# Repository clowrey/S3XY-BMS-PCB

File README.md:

# isoSPI-M3Y-BMS-PCB

**Hardware Design for Tesla Model 3/Y Battery Management System**

This repository contains the **KiCad PCB design files** for a replacement Battery Management System (BMS) designed for Tesla Model 3 and Model Y battery packs. This hardware interfaces with high-voltage (400V) battery modules using the isoSPI protocol and provides comprehensive monitoring, control, and safety features.

🔗 **Companion Firmware Repository:** [isoSPI-M3Y-BMS](https://github.com/clowrey/isoSPI-M3Y-BMS)

---

## ⚡ Overview

This PCB design implements a complete BMS controller capable of:

- **Direct BMB Communication**: isoSPI master interface for Battery Management Boards
- **High Precision Monitoring**: Current, voltage, temperature, and power measurement
- **CAN Bus Integration**: 500kbps communication with vehicle systems and inverters
- **Contactor Control**: Safe sequenced activation of high-voltage contactors
- **Cell Balancing**: Individual cell balancing control through BMB modules
- **Safety Features**: Overcurrent, overvoltage, undervoltage, and thermal protection

### 🔋 Tesla Model 3/Y Battery Pack Architecture

Tesla Model 3 and Model Y battery packs utilize a modular architecture:

- **Cell Configuration:** 4416 cells (96s46p) in 4 modules
- **Module Configuration:** 24 cells in series per module (96 total series groups)
- **Nominal Voltage:** ~350V (fully charged: ~400V, discharged: ~280V)
- **Capacity:** Varies by pack (50-82 kWh depending on model/year)
- **Battery Management Boards (BMBs):** Each module contains BMBs that monitor cell groups
- **Communication:** Original packs use proprietary Tesla BMS; this project replaces it

**Why Replace the BMS?**
- Reuse Tesla packs in DIY electric vehicle conversions
- Second-life energy storage systems
- Research and educational purposes
- Open-source alternative to proprietary systems

### 🔌 Key Hardware Features

| Feature | Implementation |
|---------|----------------|
| **Microcontroller** | Raspberry Pi RP2354B (dual Cortex-M33, 150MHz) |
| **Current Sensing** | Texas Instruments INA228 (20-bit ADC) |
| **Pack Voltage** | 4-channel ADC with precision voltage dividers |
| **CAN Interface** | Hardware CAN transceiver (500kbps) |
| **isoSPI** | Differential Manchester encoding, galvanic isolation |
| **Contactor Drivers** | 4-channel PWM with inrush control |
| **Operating Voltage** | 12V nominal input |
| **High Voltage Rating** | Up to 400V DC battery pack |

---

## 📁 Repository Structure

```
isoSPI-M3Y-BMS-PCB/
├── isoSPI-M3Y-BMS-PCB.kicad_pro    # KiCad project file
├── isoSPI-M3Y-BMS-PCB.kicad_sch    # Main schematic design
├── isoSPI-M3Y-BMS-PCB.kicad_pcb    # PCB layout
├── BMS_Library/                     # Custom component library
│   ├── BMS_Library.kicad_sym        # Symbol library
│   └── BMS_Library.pretty/          # Footprint library
├── RP2350_KiCad/                    # RP2350 MCU resources
│   ├── RP2350A_QFN-60*.kicad_mod    # Footprints
│   ├── RP2350A-QFN60.step           # 3D model
│   └── rp2350a-qfn60.kicad_sym      # Symbol
├── bms.3dshapes/                    # 3D models for connectors
├── reassociate_components.py        # Component re-linking utility
├── apply_mapping.py                 # Reference mapping tool
└── fabrication-toolkit-options.json # Manufacturing outputs config
```

---

## 🚀 Getting Started

### Prerequisites

- **KiCad 8.0+** - [Download here](https://www.kicad.org/download/)
- **Python 3.7+** (for utility scripts)
- Basic understanding of PCB design and high-voltage safety

### Opening the Project

1. **Clone the repository:**
   ```bash
   git clone https://github.com/clowrey/isoSPI-M3Y-BMS-PCB.git
   cd isoSPI-M3Y-BMS-PCB
   ```

2. **Open in KiCad:**
   - Launch KiCad
   - Open `isoSPI-M3Y-BMS-PCB.kicad_pro`

3. **Library Configuration:**
   - Libraries are configured in local `sym-lib-table` and `fp-lib-table`
   - Project-specific libraries (`BMS_Library`, `RP2350_KiCad`) should load automatically
   - If missing components appear, verify library paths in KiCad preferences

### Viewing the Design

- **Schematic:** Open `isoSPI-M3Y-BMS-PCB.kicad_sch` to view circuit design
- **PCB Layout:** Open `isoSPI-M3Y-BMS-PCB.kicad_pcb` to view board layout
- **3D View:** Press `Alt+3` in PCB editor to visualize the assembled board

---

## 🛠️ Design Sections

### Power Supply
- 12V input with protection and filtering
- 3.3V LDO for MCU and logic
- Isolated power for isoSPI interface

### Microcontroller (RP2354B)
- QFN-60 package with thermal pad
- Crystal oscillator for precision timing
- JTAG/SWD debug interface
- Boot mode selection

### Current Sensing (INA228)
- Shunt resistor-based measurement
- 20-bit delta-sigma ADC
- Bidirectional current monitoring
- I2C interface to MCU

### Voltage Monitoring
- 4-channel pack voltage measurement
- Precision resistor dividers (high voltage to ADC range)
- Individual cell voltages via isoSPI
- 12-bit internal ADC

### isoSPI Interface
- Differential transformer coupling
- Manchester encoding via PIO
- Galvanic isolation from high voltage
- Master and snooper mode support

### CAN Bus
- Hardware CAN transceiver
- 120Ω termination (configurable)
- PIO-based CAN 2.0B implementation
- 500kbps operation

### Contactor Control
- 4 independent high-current outputs
- PWM inrush current limiting
- Sequenced activation logic
- Flyback protection diodes

### Connectors
- High-voltage battery pack connector
- 12V power input
- CAN bus connector
- USB programming interface
- Debug headers

---

## 🔧 Utility Scripts

### `reassociate_components.py`

Re-links PCB footprints to schematic symbols after copying design sections. This is essential when:
- Copying and pasting PCB sections (breaks UUID links)
- Duplicating circuits for multi-channel designs
- Recovering from schematic/PCB desynchronization

**Usage:**
```bash
python reassociate_components.py
```

The script:
1. Parses both `.kicad_sch` and `.kicad_pcb` files
2. Matches components by reference designator and type
3. Updates PCB footprints with correct schematic UUIDs
4. Creates backup before modification

### `apply_mapping.py`

Applies specific component reference remapping (e.g., when renaming U11→U27). Updates both reference designators and UUID linkages.

**Usage:**
```bash
python apply_mapping.py
```

---

## 📦 Manufacturing

### Generating Production Files

The project includes `fabrication-toolkit-options.json` for automated manufacturing output generation.

**Recommended manufacturers:**
- JLCPCB
- PCBWay
- OSH Park
- Any PCB fab supporting 4+ layer boards

### PCB Specifications

| Parameter | Value |
|-----------|-------|
| **Layers** | 4 (or as designed) |
| **PCB Thickness** | 1.6mm standard |
| **Copper Weight** | 2oz for power traces |
| **Min Trace/Space** | 6/6 mil (typical) |
| **Solder Mask** | Green (or preference) |
| **Silkscreen** | White |
| **Surface Finish** | ENIG or HASL |

### High-Voltage Considerations

⚠️ **CRITICAL SAFETY REQUIREMENTS:**

- **Clearances:** Maintain minimum 4mm creepage distance for 400V
- **Isolation:** isoSPI and current sensing must maintain galvanic isolation
- **Testing:** All HV sections require hi-pot testing before energization
- **Conformal Coating:** Recommended for high-voltage traces
- **Certifications:** May require UL/CE certification for commercial use

---

## 🔌 Assembly Notes

### Component Sourcing

- Most components available from Digi-Key, Mouser, or LCSC
- RP2354B: Available from Raspberry Pi approved distributors
- INA228: Texas Instruments or authorized distributors
- Connectors: Match to Tesla pack interface specifications

### Assembly Sequence

1. **SMD Components:** Reflow solder all surface mount parts
2. **Through-hole:** Hand solder connectors and large components
3. **Inspection:** Verify all solder joints and orientation
4. **Testing:** Low-voltage functional testing before HV connection
5. **Programming:** Flash firmware via USB or SWD
6. **Calibration:** ADC and current sensing calibration routines

---

## 🔗 Firmware Integration

This PCB is designed to work with the companion firmware:

📦 **[isoSPI-M3Y-BMS Firmware](https://github.com/clowrey/isoSPI-M3Y-BMS)**

### ✅ Implemented Features (v2.0.0)

**Hardware Drivers:**
- RP2354B microcontroller with dual Cortex-M33 cores
- INA228 current/voltage/power sensor driver
- Internal ADC for pack voltage monitoring (4 channels)
- Contactor control (4 channels, sequenced activation)
- Serial command processing (30+ commands)
- CAN bus interface (can2040, 500kbps broadcast)
- isoSPI PIO master implementation
- isoSPI passive bus snooper
- Unified BMB test interface
- Runtime interface switching (Batman/isoSPI)

**System Features:**
- Parameter system with 108+ BMS parameters
- Coulomb counting for SOC tracking
- Automatic 10Hz pack status CAN broadcasting
- Statistics tracking for TX/RX/errors
- Configurable message IDs and data formatting

### 🚧 In Progress (Phase 3)

- BATMan/isoSPI interface switching
- Runtime interface control (automatic disable/enable)
- Full BMS state machine
- Cell voltage reading via isoSPI
- Cell balancing control
- Temperature monitoring

### 📋 Pending (Phases 4-6)

- Hardware testing and validation
- Calibration routines for ADC
- Flash storage for calibration data
- Error handling and recovery
- Extended testing (24+ hours)
- Performance optimization
- Documentation completion

### Getting Started with Firmware

1. Clone the firmware repository
2. Install Pico SDK and build tools (CMake-based)
3. Build the project:
   ```bash
   cd isoSPI-M3Y-BMS
   mkdir build && cd build
   cmake ..
   make
   ```
4. Flash to RP2354B via USB or SWD
5. Connect via serial interface (115200 baud)
6. Configure using serial commands
7. Optional: Integrate with ESPHome for monitoring and display

### Optional: ESPHome Display Integration

The firmware supports integration with ESPHome for advanced monitoring via touchscreen displays:

**ESPHome Features:**
- **Three-Page Display Interface:**
  - Main overview with key parameters
  - Detailed battery information
  - Cell voltage graph (all 108 cells visualized)
- **Real-time Monitoring:** Live parameter updates every 5-10 seconds
- **Touch Controls:** Balance on/off, page navigation
- **Home Assistant Integration:** All BMS parameters as HA entities
- **Professional UI:** LVGL-based interface optimized for 480x320 displays

**Supported Hardware:**
- JC4832W535 480x320 QSPI touchscreen
- ESP32-S3 based display modules
- WiFi connectivity for OTA updates

See the [ESPHome interface documentation](https://github.com/clowrey/isoSPI-M3Y-BMS/tree/main/esphome-interface) in the firmware repository for setup instructions.

---

## ⚠️ Hardware Safety

### ⚡ HIGH VOLTAGE WARNING ⚡

**This system interfaces with 400V battery packs that can deliver LETHAL current.**

- **Only qualified personnel should work on high-voltage systems**
- **Proper isolation and safety measures required**
- **Use appropriate personal protection equipment (PPE)**
- **Follow all electrical safety protocols**
- **Discharge pack completely before service**
- **EV battery systems can deliver lethal current**
- **Follow all lockout/tagout procedures**

### ⚠️ DEVELOPMENT STATUS

- **This is a development version (v2.0.0)**
- **isoSPI implementation is experimental**
- **BATMan protocol partially implemented**
- **Extensive testing required before production use**
- **USE AT YOUR OWN RISK**
- No warranty expressed or implied
- Not certified for commercial EV use
- User assumes all responsibility for safety

### Recommended Safety Equipment

- Insulated high-voltage gloves (Class 00 minimum)
- Safety glasses with side shields
- Insulated tools rated for 1000V
- Multimeter rated for CAT III 600V or higher
- Isolation transformer for bench testing
- Emergency shutdown procedures
- First aid and emergency response plan

---

## 📚 Documentation

### Related Resources

- **Firmware Repository:** [isoSPI-M3Y-BMS](https://github.com/clowrey/isoSPI-M3Y-BMS)
- **RP2354B Datasheet:** [Raspberry Pi Documentation](https://datasheets.raspberrypi.com/rp2350/rp2350-datasheet.pdf)
- **INA228 Datasheet:** [Texas Instruments](https://www.ti.com/product/INA228)
- **Pico SDK:** [Raspberry Pi Pico SDK](https://github.com/raspberrypi/pico-sdk)
- **can2040 Library:** [Kevin O'Connor's can2040](https://github.com/KevinOConnor/can2040)
- **Original BATMan BMS:** Damien Maguire & Tom de Bree

### Additional Documentation

- Schematic PDF exports (generate from KiCad)
- Bill of Materials (generate from KiCad BOM tool)
- Assembly drawings (generate from KiCad fabrication outputs)
- Test procedures (in firmware repository)
- CAN message format documentation (in firmware repo)
- Calibration procedures (in firmware repo)

---

## 🤝 Contributing

Contributions are welcome! Please:

1. Fork the repository
2. Create a feature branch (`git checkout -b feature/improvement`)
3. Make your changes with clear commit messages
4. Test thoroughly (especially high-voltage sections)
5. Submit a pull request with detailed description

**Areas for contribution:**
- Schematic improvements
- PCB layout optimization
- Additional protection circuits
- Manufacturing DFM improvements
- Documentation enhancements
- Test jig designs

---

## 📝 License

This project is licensed under the **GNU General Public License v3.0** - see the [LICENSE](LICENSE) file for details.

This program is free software: you can redistribute it and/or modify it under the terms of the GNU General Public License as published by the Free Software Foundation, either version 3 of the License, or (at your option) any later version.

This program is distributed in the hope that it will be useful, but WITHOUT ANY WARRANTY; without even the implied warranty of MERCHANTABILITY or FITNESS FOR A PARTICULAR PURPOSE. See the GNU General Public License for more details.

**In summary:**
- ✅ Free to use, modify, and distribute
- ✅ Must disclose source code
- ✅ Must use same GPL-3.0 license
- ✅ State changes made to original
- ❌ No warranty provided

---

## 🙏 Acknowledgments

- **Damien Maguire & Tom de Bree** - Original BATMan BMS software
- **ESPHome Community** - Framework and component support
- **Kevin O'Connor** - can2040 library for RP2040/RP2350
- **Raspberry Pi Foundation** - Pico SDK and excellent documentation
- **Texas Instruments** - INA228 current sensing IC
- **KiCad Community** - Excellent open-source EDA tools
- **Analog Devices** - isoSPI protocol and reference designs
- **Tesla Motors** - Battery module architecture reference

---

## 📧 Support & Contact

- **Issues:** Use GitHub Issues for bug reports and feature requests
- **Discussions:** GitHub Discussions for general questions
- **Pull Requests:** Contributions welcome via GitHub PR

---

## 📋 Changelog

### Hardware Version 2.0 (December 2025) - RP2354B Platform

**Complete platform migration supporting firmware v2.0.0:**

#### **Major Hardware Changes**

* **Microcontroller:** Migrated from ESP32 to Raspberry Pi RP2354B
  - Dual Cortex-M33 cores @ 150MHz
  - QFN-60 package with thermal management
  - Native USB support for programming and debugging
  - Hardware SWD debug interface

* **Current Sensing:** Replaced AS8510 with Texas Instruments INA228
  - 20-bit delta-sigma ADC
  - High-side and low-side sensing capability
  - I2C interface with configurable address
  - Integrated power calculation

* **Pack Voltage Monitoring:** Added 4-channel internal ADC monitoring
  - Precision voltage dividers for 400V → 3.3V range
  - 12-bit resolution
  - Individual channel filtering

* **CAN Bus:** Integrated hardware CAN transceiver
  - Native CAN 2.0B support via PIO
  - 500kbps operation
  - Configurable termination (120Ω)

#### **New Features**

* **isoSPI Implementation:**
  - Differential transformer coupling with galvanic isolation
  - PIO-based Manchester encoding/decoding
  - Master mode for direct BMB communication
  - Passive snooper mode for bus monitoring
  - Runtime switching between BATMan SPI and isoSPI

* **Enhanced Contactor Control:**
  - 4-channel PWM drivers with inrush limiting
  - Sequenced activation logic in hardware
  - Flyback protection for inductive loads

* **Unified Testing Interface:**
  - Single test connector for both BATMan and isoSPI modes
  - Automatic interface detection

#### **Firmware Compatibility**

This hardware revision requires **firmware v2.0.0 or later** from the companion repository:
- [isoSPI-M3Y-BMS v2.0.0 Changelog](https://github.com/clowrey/isoSPI-M3Y-BMS#changelog)

### Hardware Version 1.x (2024-2025) - ESP32 Platform

**Original ESP32-based design:**
- ESP32-WROOM-32 microcontroller
- AS8510 current sensor
- Arduino framework
- BATMan SPI communication only
- ESPHome integration support

---

## ⚙️ Project Status

**Current Hardware Version:** v2.0 (RP2354B-based design)

**PCB Development Status:**
- ✅ Schematic design complete
- ✅ Component selection finalized
- 🔄 PCB layout in progress
- ⏳ Design rule check (DRC) pending
- ⏳ Prototype fabrication pending
- ⏳ Hardware validation pending
- ⏳ Production testing pending

**Companion Firmware Status:** 
- **Version:** v2.0.0 (November 2025)
- **Status:** Active development
- **Phase:** isoSPI implementation in progress (Phase 3)
- **See:** [Firmware Repository](https://github.com/clowrey/isoSPI-M3Y-BMS) for detailed status

---

## 🔮 Future Enhancements

- [ ] Enhanced thermal management
- [ ] Additional redundant safety circuits
- [ ] Wireless monitoring interface
- [ ] Integrated display option
- [ ] Automotive-grade component variants
- [ ] Extended temperature range support
- [ ] Multi-pack support with CAN bridging
- [ ] Production test fixture design

---

**⚡ Building the future of open-source battery management systems ⚡**

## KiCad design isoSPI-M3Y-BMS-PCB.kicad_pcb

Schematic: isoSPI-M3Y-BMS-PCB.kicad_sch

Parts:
BT1, BT3, BT4, BT5, BT6, BT7, BT8, BT9: ~100V Brick
C1, C2, C55, C57: 10uF; C_0805_2012Metric; Voltage 50V; JLCPCB Part # C440198
C3, C4: 4.7uF 50V; C_1206_3216Metric; JLCPCB Part # C29823
C5, C94: 100nf; C_0603_1608Metric_Pad1.08x0.95mm_HandSolder; JLCPCB Part # C14663
C6, C24, C29: 10uF; C_0805_2012Metric; Voltage 50V X5R; JLCPCB Part # C440198
C7, C9, C49, C50, C51, C52, C62, C95, C132: 22uF; C_0805_2012Metric; Voltage 25V X5R; JLCPCB Part # C45783
C8: 10uF; C_0805_2012Metric_Pad1.18x1.45mm_HandSolder; Voltage 50V; JLCPCB Part # C440198
C10, C41, C42, C43: 100nf; C_0603_1608Metric; JLCPCB Part # C14663
C11, C38: 22uF; C_0805_2012Metric_Pad1.18x1.45mm_HandSolder; Voltage 25V; JLCPCB Part # C45783
C12, C13, C14, C15, C16, C21, C22, C23, C25, C28, C33, C44, C45, C54, C79, C80, C81, C82, C85: 100nF; C_0603_1608Metric; JLCPCB Part # C14663
C17, C19, C20, C86: 1uF; C_0603_1608Metric; JLCPCB Part # v
C18: 1uF; C_0603_1608Metric; JLCPCB Part # C15849
C26, C40: 1uF; C_0603_1608Metric_Pad1.08x0.95mm_HandSolder; JLCPCB Part # C15849
C27, C32, C47, C61, C69, C72: 4.7u; C_0402_1005Metric; JLCPCB Part # C23733
C30, C31, C68: 100pF; C_0603_1608Metric; JLCPCB Part # C14858
C34, C112: 680uF; CP_Radial_D10.0mm_P5.00mm; Voltage 35V Polymer
C35, C36, C117, C118: 15pF; C_0402_1005Metric; JLCPCB Part # C1548
C37, C48, C87, C89: 4.7u; C_0402_1005Metric_small_pads; JLCPCB Part # C23733
C39, C56: 100nF; C_0603_1608Metric_Pad1.08x0.95mm_HandSolder; JLCPCB Part # C14663
C46, C58, C59, C60, C63, C64, C65, C66, C67, C70, C71, C73, C74, C75, C78, C120, C123, C124, C126, C127, C128, C129, C130, C131: 100n; C_0402_1005Metric; JLCPCB Part # C1525
C53: 4.7uF; C_0603_1608Metric; JLCPCB Part # C19666
D1, D7, D10, D25: SM15T36CA; D_SMC; JLCPCB Part # C1976312
D2, D3, D4, D8, D19, D38: Green; LED_0805_2012Metric; JLCPCB Part # C2297
D5, D23, D26, D29, D31, D32, D40: White; LED_0805_2012Metric; JLCPCB Part # C34499
D6, D9, D11, D14, D15, D21, D24, D30, D36, D39, D53: SS54; D_SMA; JLCPCB Part # C22452
D12, D13, D16, D17, D18, D20, D22, D27, D41, D42, D49, D50, D51: SMB6.8CA; D_SMB; JLCPCB Part # C78395
D28, D33, D34, D37: Red; LED_0805_2012Metric; JLCPCB Part # C84256
F1, F8: Pyro Fuse
F9, F11: 63A HV DC
FB1, FB7: 120Ω@100MHz; C_0603_1608Metric; JLCPCB Part # C14709
FB5: 600R@100MHz; L_0603_1608Metric_Pad1.05x0.95mm_HandSolder; JLCPCB Part # C1002
FL3: SDCW3225S-2-102TF; FILTER-SMD_4P-L3.2-W2.5-BL; JLCPCB Part # C192586
H1, H2, H3, H4, H5, H7, H12, H13: MountingHole_Pad; MountingHole_6.5mm
J1, J10: Screw_Terminal_01x04; PhoenixContact_MC_1,5_4-G-3.81_1x04_P3.81mm_Horizontal
J2, J13: Conn_02x10_Odd_Even; PinHeader_2x10_P2.54mm_Vertical
J3: 8P8C_LED_Shielded_x2; RJ45_Amphenol_RJHSE538X-02; JLCPCB Part # C3010546
J5: OEM Shunt Connector; CONN_ZE05H-8DP-2H_HIR
J6: 349128020; CONN_SD-34912-001_02_MOL; JLCPCB Part # C587318
J7: OEM HV Sense Connector; CONN_173864-1_TYC
J8: OEM Connector; S44BRAD1AK
J9, J16: Conn_01x03; PinHeader_1x03_P2.54mm_Vertical
J11: Screw_Terminal_01x03; PhoenixContact_MC_1,5_2-G-3.81_1x02_P3.81mm_Horizontal
J12: Screw_Terminal_01x08; PhoenixContact_MC_1,5_8-G-3.81_1x08_P3.81mm_Horizontal
J14: Screw_Terminal_01x04; PhoenixContact_GMSTBA_2,5_4-G-7,62_1x04_P7.62mm_Horizontal
J15, J17, J18: USB_C_Receptacle_USB2.0_16P; USB_C_Receptacle_HRO_TYPE-C-31-M-12
JP1, JP2, JP7, JP8, JP9: SolderJumper_3_Bridged12; SolderJumper-3_P1.3mm_Bridged12_RoundedPad1.0x1.5mm_NumberL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
JP3, JP4, JP5, JP6, JP13, JP14: SolderJumper_3_Open; SolderJumper-3_P1.3mm_Open_RoundedPad1.0x1.5mm_NumberLabels
JP10, JP11, JP12: Jumper_2_Open; SolderJumper-2_P1.3mm_Open_RoundedPad1.0x1.5mm
K9, K14: Link Positive
K10, K16: FC Positive
K11, K17: FC Negative
K12, K15: Link Negative
K13, K18: Inverter
L1, L2, L4, L5: 6.8uh; L_Changjiang_FXL0630; JLCPCB Part # C167221
L3, L8: 22uh 5.5A; L_Changjiang_FXL1040; JLCPCB Part # C475917
L6, L7: 3.3u; L_pol_2016
Q1, Q2, Q3, Q5: CRSM034N06L2; AO_DFN-8-1EP_5.55x5.2mm_P1.27mm_EP4.12x4.6mm; JLCPCB Part # C467174
R1, R10: 150r; R_0603_1608Metric; JLCPCB Part # C22808
R2, R8: 2.2k; R_0603_1608Metric; JLCPCB Part # C4190
R3, R11, R27, R40, R41, R45, R47, R70, R74, R146: 24k; R_0603_1608Metric; JLCPCB Part # C23352
R4, R17, R25, R28, R62, R150: 100k; R_0603_1608Metric; JLCPCB Part # C25803
R5, R6, R26, R69, R90: 100R; R_0603_1608Metric; JLCPCB Part # C22775
R7, R9, R111, R112, R141: 510r; R_0603_1608Metric; JLCPCB Part # C23193
R12, R13, R14, R15, R20, R44, R53, R55, R82, R85, R174, R175: 5.1k; R_0603_1608Metric; JLCPCB Part # C23186
R16, R29, R48, R54, R56, R60, R66, R67, R68, R75, R77, R79, R83, R84, R140, R142, R143, R144, R148, R190: 10k; R_0603_1608Metric; JLCPCB Part # C25804
R18: 120r; R_1206_3216Metric; JLCPCB Part # C17909
R19, R33, R50, R58, R80, R171: 33r; R_0402_1005Metric; JLCPCB Part # C25105
R21, R24, R51, R52: 22R; R_0402_1005Metric; JLCPCB Part # C25092
R22, R31, R81: 10k; R_0603_1608Metric_Pad0.98x0.95mm_HandSolder; JLCPCB Part # C25804
R23, R36, R37, R38, R39, R42: 1.8k; R_0603_1608Metric; JLCPCB Part # C4177
R30: 100r; R_0603_1608Metric; JLCPCB Part # C22775
R32, R178: 25296nΩ
R34, R35, R43, R46, R49, R57, R59, R63, R64, R167, R168, R170: 1k; R_0402_1005Metric; JLCPCB Part # C11702
R61: 3k; R_0603_1608Metric; JLCPCB Part # C4211
R65: 2.7k; R_0603_1608Metric; JLCPCB Part # C13167
R94, R97: 1k; R_0603_1608Metric; JLCPCB Part # C21190
R98, R99, R100, R101, R102, R103, R104, R105, R106, R107, R108, R109, R110, R114, R115, R116, R126, R127, R130, R131, R134, R135, R153, R155, R193, R194, R195, R196, R214, R215, R216, R217, R218, R219, R220, R221, R222, R223, R224, R225, R226, R227: 1M; R_1206_3216Metric; JLCPCB Part # C17927
R149, R228, R229: 220r; R_0603_1608Metric; JLCPCB Part # C22962
R176: 27R 50W
SW1, SW2, SW3, SW4: TS-1187A-B-A-B; SW_Push_1P1T_XKB_TS-1187A; JLCPCB Part # C318884
TH1, TH2, TH3, TH4, TH5, TH6: B59451C1130B070; RV_Disc_D15.5mm_W7.5mm_P5.0mm; JLCPCB Part # C2762811
TP1, TP2, TP3, TP4, TP5, TP6, TP7, TP8, TP9, TP15, TP17, TP18: TestPoint_2Pole; TestPoint_2Pads_Pitch2.54mm_Drill0.9mm
TP10, TP11, TP12, TP13, TP14: TP; TestPoint_THTPad_D1.5mm_Drill1.0mm
TR10: HM2113ZNLT; JLCPCB Part # C5730533
U1, U15, U23, U25, U26: SN74LV1T08DBVR; SOT-23-5; JLCPCB Part # C2682144
U2, U4, U30: ISO1540; SOIC-8_3.9x4.9mm_P1.27mm; JLCPCB Part # C179739
U3: INA228; VSSOP-10_3x3mm_P0.5mm; JLCPCB Part # C5214669
U6, U22, U24: F0505S-1WR3; Converter_DCDC_TRACO_TEA1-xxxxHI_THT; JLCPCB Part # C7465182
U8, U9, U10, U20: LTV-217-B-G; SSOP-4_4.4x2.6mm_P1.27mm; JLCPCB Part # C115450
U11, U27: RP2354B; RP2350-QFN-80-1EP_10x10_P0.4mm_EP3.4x3.4mm_ThermalVias; JLCPCB Part # C39843328
U12: ADS1115; TSSOP-10_3x3mm_P0.5mm; LCSC Part # C37593
U13: ISO1050DUB; SOP-8_6.62x9.15mm_P2.54mm; LCSC Part # C16428
U16: BatMan; LQFP-64_10x10mm_P0.5mm; JLCPCB Part # DNP
U17: TPS5430DDAR; TI_SO-PowerPAD-8_ThermalVias; LCSC Part C9864
U21: AMS1117-3.3; SOT-223-3_TabPin2; JLCPCB Part # C6186
U28: AM26LV32EIDR; SOIC-16_3.9x9.9mm_P1.27mm; JLCPCB Part # C527448
U29: B0505S-3WR2; Converter_DCDC_TRACO_TRA3-xxxx_THT; LCSC Part # C7500927
U32: SP3485EN-L/TR; SOIC-8_3.9x4.9mm_P1.27mm; JLCPCB Part # C8963
Y1, Y2: ABM8-272-T3; Crystal_SMD_3225-4Pin_3.2x2.5mm; JLCPCB Part # C20625731

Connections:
3.3V Sense: R66.2, R67.1, U27.49 (GPIO40_ADC0)
5V Sense: R140.1, R146.2, U27.52 (GPIO41_ADC1)
+1V1: C48.1, C71.1, C120.1, C123.1, L7.1, U27.10 (DVDD), U27.32 (DVDD), U27.51 (DVDD), U27.65 (VREG_FB)
+1V1_2: C46.1, C58.1, C70.1, C87.1, L6.1, U11.10 (DVDD), U11.32 (DVDD), U11.51 (DVDD), U11.65 (VREG_FB)
+3.3V: C13.1, C14.1, C37.1, C53.2, C59.1, C60.1, C63.1, C64.1, C65.1, C66.1, C67.1, C73.1, C74.1, C75.1, C78.1, C89.1, C124.1, C126.1, C127.1, C128.1, C129.1, C130.1, C131.1, J2.1, J2.3, J2.5, J2.7, J2.9, J13.1, J13.3, J13.5, J13.7, J13.9, R12.1, R13.1, R19.2, R33.2, R50.2, R58.2, R59.1, R65.2, R66.1, R75.1, R82.1, R85.1, R94.1, TP7.2, U2.1 (VCC1), U4.1 (VCC1), U8.4, U9.4, U11.5 (IOVDD), U11.15 (IOVDD), U11.24 (IOVDD), U11.29 (IOVDD), U11.41 (IOVDD), U11.50 (IOVDD), U11.60 (IOVDD), U11.64 (VREG_VIN), U11.68 (USB_OTP_VDD), U11.69 (QSPI_IOVDD), U11.76 (IOVDD), U13.1 (VCC1), U21.2 (VO), U27.5 (IOVDD), U27.15 (IOVDD), U27.24 (IOVDD), U27.29 (IOVDD), U27.41 (IOVDD), U27.50 (IOVDD), U27.60 (IOVDD), U27.64 (VREG_VIN), U27.68 (USB_OTP_VDD), U27.69 (QSPI_IOVDD), U27.76 (IOVDD), U30.1 (VCC1)
+3V3: C21.1, C22.2, C25.1, U1.5 (VCC), U28.4 (G), U28.16 (VDD), U32.8 (VCC)
+5V: C9.2, C11.2, C23.1, C49.2, C50.2, C52.2, C79.2, C80.2, C81.2, C82.2, C112.1, C132.2, FB1.2, FB7.2, L1.2, L2.2, L4.2, L5.2, L8.1, R60.1, R146.1, R190.1, TP8.2, U15.5 (VCC), U16.5 (5V), U16.41 (5V), U16.47 (5V), U21.3 (VI), U23.5 (VCC), U25.5 (VCC), U26.5 (VCC)
/CAN 5V: C6.2, C16.2, R23.2, R37.2, R77.1, R112.1, U13.8 (VCC2), U24.7 (+Vout)
/CAN H: C30.2, D16.2 (A2), FL3.2, JP1.3 (B), JP2.1 (A), JP3.3 (B), JP4.3 (B), JP5.3 (B), JP6.3 (B), JP13.3 (B), JP14.3 (B), R18.2, TP2.2
/CAN L: C31.1, D17.1 (A1), FL3.3, JP1.1 (A), JP2.3 (B), JP3.1 (A), JP4.1 (A), JP5.1 (A), JP6.1 (A), JP13.1 (A), JP14.1 (A), R18.1, TP2.1
/Contactor_Input: D15.2 (A), D20.2 (A2), D36.2 (A), J1.2
/FC Pos: K10.13, K16.13, K18.1, R176.2, TH1.2, TH2.2, TH3.2
/FC-Neg-Jumper: C44.2, D19.1 (K), D25.2 (A2), D39.2 (A), JP10.1 (A), JP11.1 (A), JP12.1 (A), Q3.5 (D)
/GPIO0: R57.2, U27.77 (GPIO0)
/GPIO1: R63.2, U27.78 (GPIO1)
/GPIO2: R64.2, U27.79 (GPIO2)
/GPIO3: U27.80 (GPIO3)
/GPIO4: J2.2, U27.1 (GPIO4)
/GPIO5: J2.4, U27.2 (GPIO5)
/GPIO6: J2.6, U27.3 (GPIO6)
/GPIO7: J2.8, U27.4 (GPIO7)
/GPIO8: J2.10, U27.6 (GPIO8)
/GPIO9: J2.12, U27.7 (GPIO9)
/GPIO10: J2.14, U27.8 (GPIO10)
/GPIO11: J2.16, U27.9 (GPIO11)
/GPIO12: J2.18, U27.11 (GPIO12)
/GPIO13: J2.20, U27.12 (GPIO13)
/GPIO14: U27.13 (GPIO14)
/GPIO15: U27.14 (GPIO15)
/GPIO16: U27.16 (GPIO16)
/GPIO17: U27.17 (GPIO17)
/GPIO18: U27.18 (GPIO18)
/GPIO19: U27.19 (GPIO19)
/GPIO20: U27.20 (GPIO20)
/GPIO21: U27.21 (GPIO21)
/GPIO22: U27.22 (GPIO22)
/GPIO23: U27.23 (GPIO23)
/GPIO24: U27.25 (GPIO24)
/GPIO25: R48.1, U27.26 (GPIO25)
/GPIO44_ADC4: U27.55 (GPIO44_ADC4)
/GPIO45_ADC5: U27.56 (GPIO45_ADC5)
/GPIO46_ADC6: U27.57 (GPIO46_ADC6)
/GPIO47_ADC7: U27.58 (GPIO47_ADC7)
/Grn: J3.6, JP14.2 (C)
/HV Sense 5V: C18.2, C39.2, C56.2, FB5.2, R20.1, R44.1, R54.1, R81.2, R228.1, U2.8 (VCC2), U12.8 (VDD)
/Logic_Input: D12.2 (A2), D14.2 (A), J1.4
/MCU2_GPIO0: R59.2, U11.77 (GPIO0)
/MCU2_GPIO3: U11.80 (GPIO3)
/MCU2_GPIO4: J13.2, U11.1 (GPIO4)
/MCU2_GPIO5: J13.4, U11.2 (GPIO5)
/MCU2_GPIO6: J13.6, U11.3 (GPIO6)
/MCU2_GPIO7: J13.8, U11.4 (GPIO7)
/MCU2_GPIO8: J13.10, U11.6 (GPIO8)
/MCU2_GPIO9: J13.12, U11.7 (GPIO9)
/MCU2_GPIO10: J13.14, U11.8 (GPIO10)
/MCU2_GPIO11: J13.16, U11.9 (GPIO11)
/MCU2_GPIO12: J13.18, U11.11 (GPIO12)
/MCU2_GPIO13: J13.20, U11.12 (GPIO13)
/MCU2_GPIO15: U11.14 (GPIO15)
/MCU2_GPIO16: U11.16 (GPIO16)
/MCU2_GPIO17: U11.17 (GPIO17)
/MCU2_GPIO18: U11.18 (GPIO18)
/MCU2_GPIO19: U11.19 (GPIO19)
/MCU2_GPIO20: U11.20 (GPIO20)
/MCU2_GPIO21: U11.21 (GPIO21)
/MCU2_GPIO22: U11.22 (GPIO22)
/MCU2_GPIO23: U11.23 (GPIO23)
/MCU2_GPIO24: U11.25 (GPIO24)
/MCU2_GPIO25: R56.1, U11.26 (GPIO25)
/MCU2_GPIO26: U11.27 (GPIO26)
/MCU2_GPIO27: U11.28 (GPIO27)
/MCU2_GPIO28: U11.36 (GPIO28)
/MCU2_GPIO29: U11.37 (GPIO29)
/MCU2_GPIO30: U11.38 (GPIO30)
/MCU2_GPIO31: U11.39 (GPIO31)
/MCU2_GPIO32: U11.40 (GPIO32)
/MCU2_GPIO33: U11.42 (GPIO33)
/MCU2_GPIO34: U11.43 (GPIO34)
/MCU2_GPIO35: U11.44 (GPIO35)
/MCU2_GPIO36: U11.45 (GPIO36)
/MCU2_GPIO37: U11.46 (GPIO37)
/MCU2_GPIO38: R34.2, U11.47 (GPIO38)
/MCU2_GPIO39: R35.2, U11.48 (GPIO39)
/PH: C54.1, D24.1 (K), L8.2, U17.8 (PH)
/QSPI2_SCLK: U11.71 (QSPI_SCLK)
/QSPI2_SD0: U11.72 (QSPI_SD0)
/QSPI2_SD1: U11.74 (QSPI_SD1)
/QSPI2_SD2: U11.73 (QSPI_SD2)
/QSPI2_SD3: U11.70 (QSPI_SD3)
/QSPI2_SS: R49.1, U11.75 (QSPI_SS)
/QSPI_SCLK: U27.71 (QSPI_SCLK)
/QSPI_SD0: U27.72 (QSPI_SD0)
/QSPI_SD1: U27.74 (QSPI_SD1)
/QSPI_SD2: U27.73 (QSPI_SD2)
/QSPI_SD3: U27.70 (QSPI_SD3)
/QSPI_SS: R170.1, U27.75 (QSPI_SS)
/RUN: R167.2, SW4.2
/RUN_2: R43.1, U11.35 (RUN)
/SWCLK: J16.1, U27.33 (SWCLK)
/SWCLK_2: J9.1, U11.33 (SWCLK)
/SWD: J16.3, U27.34 (SWD)
/SWD_2: J9.3, U11.34 (SWD)
/Serial API 5V: C12.2, C24.2, D21.2 (A), R97.1, R141.1, R142.1, U29.6 (+Vout), U30.8 (VCC2)
/Serial API RX: D42.1 (A1), J15.A6 (D+), J15.B6 (D+), R143.1, U30.6 (SCL2)
/Serial API TX: D41.2 (A2), J15.A7 (D-), J15.B7 (D-), R97.2, U30.7 (SDA2)
/USB2_D+: J17.A6 (D+), J17.B6 (D+), R51.1
/USB2_D-: J17.A7 (D-), J17.B7 (D-), R52.1
/USB_D+: J18.A6 (D+), J18.B6 (D+), R21.1
/USB_D-: J18.A7 (D-), J18.B7 (D-), R24.1
/VREG2_AVDD: C32.1, R33.1, U11.61 (VREG_AVDD)
/VREG2_LX: L6.2, U11.63 (VREG_LX)
/VREG_AVDD: C61.1, R19.1, U27.61 (VREG_AVDD)
/VREG_LX: L7.2, U27.63 (VREG_LX)
/V_cont1: C2.2, D15.1 (K), D36.1 (K), L3.2
/Wht-Grn: J3.3, JP13.2 (C)
/XIN: C117.1, U27.30 (XIN), Y2.1
/XIN_2: C35.1, U11.30 (XIN), Y1.1
/XOUT: R168.1, U27.31 (XOUT)
/XOUT_2: R46.1, U11.31 (XOUT)
/iso+: C68.2, JP7.2 (C), R90.1, TP18.1, TR10.1 (TD-)
/iso-: C68.1, JP8.2 (C), R90.2, TP18.2, TR10.3 (TD+)
BatSPI_EN: U16.42 (EN), U27.46 (GPIO37)
BatSPI_SCK: U16.56 (SPI_SCK), U27.43 (GPIO34)
Batman IsoSPI+: JP8.3 (B), U16.62 (A-BMB)
Batman IsoSPI-: JP7.3 (B), U16.61 (A-BMB)
Batt Negative: J7.10, J14.4, R225.2
Batt Positive: J7.1, J14.1, R224.2
C FC-Neg (GND): J8.37, J12.2, JP10.2 (B), JP11.2 (B), JP12.2 (B)
C FC-Pos (GND): C33.2, D1.2 (A2), D4.1 (K), D11.2 (A), J8.36, J12.4, Q2.5 (D)
C Neg (GND): C15.2, D3.1 (K), D6.2 (A), D7.2 (A2), J8.42, J12.6, Q1.5 (D)
C Pos (GND): C45.2, D8.1 (K), D9.2 (A), D10.2 (A2), J8.41, J12.8, Q5.5 (D)
CAN Rx: R83.1, TP6.1, U13.2 (RXD)
CAN Tx: R84.1, TP6.2, U13.3 (TXD)
C_En: U11.13 (GPIO14), U15.2, U23.2, U25.2, U26.2
Drive Unit Pos: F9.1, K9.13, K10.14, K14.13, K16.14, TH4.1, TH5.1, TH6.1
Emergency Stop: R22.2, U8.3
Extra Input: R31.2, U9.3
Extra Output 1: R39.2
Extra Output 2: R38.2
FC Negative: J7.7, J14.3, R227.2
FC Positive: J7.4, J14.2, R226.2
FC-Neg: U26.1
FC-Pos: U25.1
GND: C1.1, C2.1, C7.1, C9.1, C11.1, C13.2, C14.2, C15.1, C21.2, C22.1, C23.2, C25.2, C27.2, C32.2, C33.1, C34.2, C35.2, C36.2, C37.2, C38.1, C44.1, C45.1, C46.2, C47.2, C48.2, C49.1, C50.1, C51.1, C52.1, C53.1, C55.1, C57.1, C58.2, C59.2, C60.2, C61.2, C62.1, C63.2, C64.2, C65.2, C66.2, C67.2, C69.2, C70.2, C71.2, C72.2, C73.2, C74.2, C75.2, C78.2, C79.1, C80.1, C81.1, C82.1, C85.1, C87.2, C89.2, C112.2, C117.2, C118.2, C120.2, C123.2, C124.2, C126.2, C127.2, C128.2, C129.2, C130.2, C131.2, C132.1, D1.1 (A1), D2.1 (K), D5.1 (K), D7.1 (A1), D10.1 (A1), D22.1 (A1), D23.1 (K), D24.2 (A), D25.1 (A1), D26.1 (K), D28.1 (K), D33.1 (K), D34.1 (K), D37.1 (K), D49.1 (A1), D51.1 (A1), J1.1, J1.3, J2.11, J2.13, J2.15, J2.17, J2.19, J9.2, J13.11, J13.13, J13.15, J13.17, J13.19, J16.2, J17.A1 (GND), J17.A12 (GND), J17.B1 (GND), J17.B12 (GND), J17.S1 (SHIELD), J18.A1 (GND), J18.A12 (GND), J18.B1 (GND), J18.B12 (GND), J18.S1 (SHIELD), Q1.1 (S), Q1.2 (S), Q1.3 (S), Q2.1 (S), Q2.2 (S), Q2.3 (S), Q3.1 (S), Q3.2 (S), Q3.3 (S), Q5.1 (S), Q5.2 (S), Q5.3 (S), R4.1, R17.1, R22.1, R25.1, R29.2, R31.1, R53.1, R55.1, R57.1, R62.1, R67.2, R99.1, R140.2, R148.2, R149.2, R174.1, R175.1, SW1.1, SW2.1, SW3.1, SW4.1, TP7.1, TP8.1, U1.3 (GND), U2.4 (GND1), U4.4 (GND1), U6.2 (-Vin), U10.2, U11.62 (VREG_PGND), U11.81 (GND), U13.4 (GND1), U15.3 (GND), U16.1 (GND), U16.3 (GND), U16.6 (GND), U16.7 (GND), U16.8 (GND), U16.9 (GND), U16.10 (GND), U16.11 (GND), U16.12 (GND), U16.13 (GND), U16.14 (GND), U16.15 (GND), U16.16 (GND), U16.17 (GND), U16.18 (GND), U16.19 (GND), U16.20 (GND), U16.21 (GND), U16.22 (GND), U16.23 (GND), U16.24 (GND), U16.25 (GND), U16.26 (GND), U16.27 (GND), U16.28 (GND), U16.29 (GND), U16.30 (GND), U16.31 (GND), U16.33 (GND), U16.34 (GND), U16.35 (GND), U16.36 (GND), U16.37 (GND), U16.38 (GND), U16.39 (GND), U16.40 (GND), U16.43 (GND), U16.45 (GND), U16.46 (GND), U16.49 (GND), U16.51 (GND), U16.60 (GND), U17.6 (GND), U17.9 (PowerPAD), U20.2, U21.1 (GND), U22.2 (-Vin), U23.3 (GND), U24.2 (-Vin), U25.3 (GND), U26.3 (GND), U27.62 (VREG_PGND), U27.81 (GND), U28.8 (GND), U28.12 (~G), U29.2 (-Vin), U30.4 (GND1), U32.2 (~RE), U32.5 (GND), Y1.2, Y1.4, Y2.2, Y2.4
GND CAN: C6.1, C16.1, C30.1, C31.2, D16.1 (A1), D17.2 (A2), D29.1 (K), J3.19, J3.SH, R112.2, U13.5 (GND2), U24.5 (-Vout)
GND_RS: C12.1, C24.1, D38.1 (K), D40.1 (K), D41.1 (A1), D42.2 (A2), J15.A1 (GND), J15.A12 (GND), J15.B1 (GND), J15.B12 (GND), J15.S1 (SHIELD), R141.2, U29.4 (-Vout), U30.5 (GND2)
GND_VSens: C8.1, C18.1, C39.1, C56.1, C95.1, D32.1 (K), R229.2, TP12.1, U2.5 (GND2), U6.5 (-Vout), U12.1 (ADDR), U12.3 (GND)
HMI Serial RX: R35.1, R94.2, TP5.2, U27.48 (GPIO39), U30.3 (SCL1)
HMI Serial TX: R34.1, R144.1, TP5.1, U27.47 (GPIO38), U30.2 (SDA1)
I2C SCL Shunt: R12.2, TP3.2, U4.3 (SCL1)
I2C SCL Vsense: R82.2, TP4.2, U2.3 (SCL1)
I2C SDA Shunt: R13.2, TP3.1, U4.2 (SDA1)
I2C SDA Vsense: R85.2, TP4.1, U2.2 (SDA1)
IsoSPI RX AND: U1.4, U27.38 (GPIO30)
IsoSPI RX Debug: U27.39 (GPIO31)
IsoSPI RX H: TP17.1, U1.2, U27.36 (GPIO28), U28.5 (2Y)
IsoSPI RX L: TP17.2, U1.1, U27.37 (GPIO29), U28.3 (1Y)
IsoSPI TX Data: TP1.2, U27.28 (GPIO27), U32.4 (DI)
IsoSPI TX En: TP1.1, U27.27 (GPIO26), U32.3 (DE)
IsoSPI+: J6.1, J11.1, TR10.4 (TX+)
IsoSPI-: J6.2, J11.2, TR10.6 (TX-)
Link Negative: J7.22
Link Positive: J7.13
MUC1-MCU2 TX-RX: R63.1, TP9.2, U11.79 (GPIO2)
MUC2-MCU1 TX-RX: R64.1, TP9.1, U11.78 (GPIO1)
Neg: U23.1
unnamed: BT1.1 (+), BT5.2 (-)
unnamed: BT1.2 (-), R32.2
unnamed: BT3.1 (+), F8.1
unnamed: BT3.2 (-), BT4.1 (+)
unnamed: BT4.2 (-), BT9.2 (-), K12.14, K15.14
unnamed: BT5.1 (+), BT6.1 (+), K9.14, K14.14, R176.1
unnamed: BT6.2 (-), BT7.1 (+)
unnamed: BT7.2 (-), R178.1
unnamed: BT8.1 (+), F1.1
unnamed: BT8.2 (-), BT9.1 (+)
unnamed: C3.2, R8.2, R10.1
unnamed: C4.1, R1.1, R2.2
unnamed: C10.1, C41.2, C42.1, C43.2, C95.2, R40.2, R41.1, R45.2, R47.1, R228.2, R229.1
unnamed: C26.1, J3.14, J3.23, U9.2
unnamed: C26.2, R36.1, U9.1
unnamed: C27.1, R50.1, R80.2
unnamed: C36.1, R46.2, Y1.3
unnamed: C40.1, J3.20, J3.21, U8.2
unnamed: C40.2, R23.1, U8.1
unnamed: C69.1, R58.1, R171.2
unnamed: C118.1, R168.2, Y2.3
unnamed: D2.2 (A), R83.2
unnamed: D3.2 (A), R11.2
unnamed: D4.2 (A), R27.2
unnamed: D5.2 (A), R74.2
unnamed: D8.2 (A), R3.2
unnamed: D12.1 (A1), D13.2 (A2)
unnamed: D13.1 (A1), D22.2 (A2)
unnamed: D18.1 (A1), D50.2 (A2)
unnamed: D19.2 (A), R70.2
unnamed: D20.1 (A1), D27.2 (A2)
unnamed: D21.1 (K), J15.A4 (VBUS), J15.A9 (VBUS), J15.B4 (VBUS), J15.B9 (VBUS)
unnamed: D23.2 (A), R190.2
unnamed: D26.2 (A), R75.2
unnamed: D27.1 (A1), D49.2 (A2)
unnamed: D28.2 (A), R84.2
unnamed: D29.2 (A), R77.2
unnamed: D30.2 (A), J17.A4 (VBUS), J17.A9 (VBUS), J17.B4 (VBUS), J17.B9 (VBUS)
unnamed: D30.1 (K), FB1.1
unnamed: D31.2 (A), R79.2
unnamed: D32.2 (A), R81.1
unnamed: D33.2 (A), R48.2
unnamed: D34.2 (A), R56.2
unnamed: D37.2 (A), R144.2
unnamed: D38.2 (A), R143.2
unnamed: D40.2 (A), R142.2
unnamed: D50.1 (A1), D51.2 (A2)
unnamed: D53.2 (A), J18.A4 (VBUS), J18.A9 (VBUS), J18.B4 (VBUS), J18.B9 (VBUS)
unnamed: D53.1 (K), FB7.1
unnamed: F1.2, R178.4
unnamed: F8.2, R32.1
unnamed: F9.2, K13.1
unnamed: F11.1, K11.14, K12.13, K13.2, K15.13, K17.14
unnamed: F11.2, K11.13, K17.13, K18.2
unnamed: J3.13, R36.2, R42.2
unnamed: J3.15, U20.4
unnamed: J3.16, U10.3
unnamed: J3.17, U10.4
unnamed: J3.18, U20.3
unnamed: J3.22, R37.1
unnamed: J3.24, R42.1
unnamed: J17.A5 (CC1), R53.2
unnamed: J17.B5 (CC2), R55.2
unnamed: J18.A5 (CC1), R174.2
unnamed: J18.B5 (CC2), R175.2
unnamed: J3.5, JP1.2 (C)
unnamed: J3.4, JP2.2 (C)
unnamed: J3.8, JP3.2 (C)
unnamed: J3.7, JP4.2 (C)
unnamed: J3.2, JP5.2 (C)
unnamed: J3.1, JP6.2 (C)
unnamed: C20.1, C86.1, JP7.1 (A), U32.6 (A)
unnamed: C17.1, C19.1, JP8.1 (A), U32.7 (B)
unnamed: C85.2, JP9.1 (A)
unnamed: JP9.2 (C), TR10.2 (C_TD)
unnamed: Q1.4 (G), R5.2
unnamed: Q2.4 (G), R6.2
unnamed: Q3.4 (G), R69.2
unnamed: Q5.4 (G), R26.2
unnamed: R4.2, R5.1, U23.4
unnamed: R6.1, R17.2, U25.4
unnamed: R25.2, R26.1, U15.4
unnamed: R30.1, U16.64 (B-BMB)
unnamed: R30.2, U16.63 (B-BMB)
unnamed: R38.1, U20.1
unnamed: R39.1, U10.1
unnamed: R43.2, SW2.2
unnamed: R49.2, SW1.2
unnamed: R62.2, R69.1, U26.4
unnamed: R98.1, R99.2
unnamed: R100.2, R104.1
unnamed: R101.2, R105.1
unnamed: R102.2, R106.1
unnamed: R103.2, R107.1
unnamed: R104.2, R108.1
unnamed: R105.2, R109.1
unnamed: R106.2, R110.1
unnamed: R107.2, R114.1
unnamed: R108.2, R115.1
unnamed: R109.2, R116.1
unnamed: R110.2, R126.1
unnamed: R114.2, R127.1
unnamed: R115.2, R130.1
unnamed: R116.2, R131.1
unnamed: R126.2, R134.1
unnamed: R127.2, R135.1
unnamed: R130.2, R153.1
unnamed: R131.2, R155.1
unnamed: R134.2, R193.1
unnamed: R135.2, R194.1
unnamed: R61.2, R149.1
unnamed: R153.2, R195.1
unnamed: R155.2, R196.1
unnamed: R170.2, SW3.2
unnamed: R193.2, R214.1
unnamed: R194.2, R215.1
unnamed: R195.2, R216.1
unnamed: R196.2, R217.1
unnamed: R214.2, R218.1
unnamed: R215.2, R219.1
unnamed: R216.2, R220.1
unnamed: R217.2, R221.1
unnamed: R218.2, R222.1
unnamed: R219.2, R223.1
unnamed: R220.2, R224.1
unnamed: R221.2, R225.1
unnamed: R222.2, R226.1
unnamed: R223.2, R227.1
unnamed: TH1.1, TH2.1, TH3.1, TH4.2, TH5.2, TH6.2
unnamed: R98.2, TR10.5 (C_TX)
unnamed: R15.2, U3.5 (SCL), U4.6 (SCL2)
unnamed: R14.2, U3.4 (SDA), U4.7 (SDA2)
unnamed: C5.2, R2.1, U3.10 (Vin+)
unnamed: C5.1, R8.1, U3.9 (Vin-)
unnamed: R68.2, U3.3 (~Alert)
unnamed: C38.2, L2.1, U6.1 (+Vin)
unnamed: C8.2, FB5.1, U6.7 (+Vout)
unnamed: C47.1, R80.1, U11.59 (ADC_AVDD)
unnamed: R52.2, U11.66 (USB_DM)
unnamed: R51.2, U11.67 (USB_DP)
unnamed: C10.2, R40.1, R100.1, TP14.1, U12.4 (AIN0)
unnamed: C41.1, R41.2, R101.1, TP13.1, U12.5 (AIN1)
unnamed: C42.2, R45.1, R102.1, TP11.1, U12.6 (AIN2)
unnamed: C43.1, R47.2, R103.1, TP10.1, U12.7 (AIN3)
unnamed: R54.2, U12.2 (ALERT/RDY)
unnamed: R44.2, U2.6 (SCL2), U12.10 (SCL)
unnamed: R20.2, U2.7 (SDA2), U12.9 (SDA)
unnamed: FL3.1, U13.7 (CANH)
unnamed: FL3.4, U13.6 (CANL)
unnamed: C54.2, U17.1 (BOOT)
unnamed: R60.2, R61.1, U17.4 (VSENSE)
unnamed: C7.2, L1.1, U22.1 (+Vin)
unnamed: C62.2, L5.1, U24.1 (+Vin)
unnamed: C72.1, R171.1, U27.59 (ADC_AVDD)
unnamed: R167.1, U27.35 (RUN)
unnamed: R24.2, U27.66 (USB_DM)
unnamed: R21.2, U27.67 (USB_DP)
unnamed: C86.2, U28.2 (1A)
unnamed: C17.2, U28.1 (1B)
unnamed: C19.2, U28.6 (2A)
unnamed: C20.2, U28.7 (2B)
unnamed: C51.2, L4.1, U29.1 (+Vin)
Pos: U15.1
Shunt Midpoint: J5.8
Shunt NTC +: C94.2, J5.7, J10.1, R16.1, U3.8 (Vbus)
Shunt NTC -: C3.1, C4.2, C28.1, C29.1, C94.1, D31.1 (K), J5.1, J5.3, J10.2, R7.1, R9.2, R111.2, U3.1 (A1), U3.2 (A0), U3.7 (GND), U4.5 (GND2), U22.5 (-Vout)
Shunt Passive +: J5.6
Shunt Sense +: J5.5, J10.3, R1.2, R7.2
Shunt Sense -: J5.4, J10.4, R9.1, R10.2
Shunt_5V: C28.2, C29.2, R14.1, R15.1, R16.2, R68.1, R79.1, R111.1, U3.6 (VS), U4.8 (VCC2), U22.7 (+Vout)
Snooper Debug: U27.40 (GPIO32)
VContactor Sense: R28.1, R29.1, U27.54 (GPIO43_ADC3)
V_{Contactor}: C1.2, C34.1, D6.1 (K), D9.1 (K), D11.1 (K), D18.2 (A2), D39.1 (K), J8.33, J8.34, J8.35, J8.43, J12.1, J12.3, J12.5, J12.7, L3.1, R3.1, R11.1, R27.1, R28.2, R70.1
V_{in}: C55.2, C57.2, D14.1 (K), R74.1, R150.2, U17.7 (VIN)
Vin Logic Sense: R148.1, R150.1, U27.53 (GPIO42_ADC2)

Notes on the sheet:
all JLC basic components
3.3V 1A LDO Supply
GPIO4 - GPIO13 on NC header
FC Negative Contactor
Would be cool if it alternates with main
PTC 440V 56Ω
BMB side xfmr center tap has no connection reference to ground to prevent ESD
unused inputs left floating - internal bias
3A max output - 3.3V draws from this rail
Galvanically Isolated Area
100k input impedance 0.14mA typical ADC usage
Terminate unused port per LTC6813 datasheet (100R recommended)
MCU Identification
In tesla packs the shunt is at the mid point of the pack!
Supervisor MCU
5V powers exteral ESP32 LCD also
FC Positive Contactor
Cells Positive Contactor
close to MCU
Extra GPIO
API TTL RS232 Interface
Redundant connectors
isoSPI Transceiver
Shunt Current Sense
Cells Positive Always Live
10V-16V input
Data must be after En
Positives
all JLC basic components except: inductor, 680uf cap
1A max output
Inverter connected to FC port
5V 3A DC-DC Supply
5V 600mA max external ESP32 interface
BatMan Interface
Inverter CAN Interface
Cells Negative Contactor
I2C ADDR: 0x48
requires connection to always live terminal
Contactor AND gate enable output
Main MCU

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
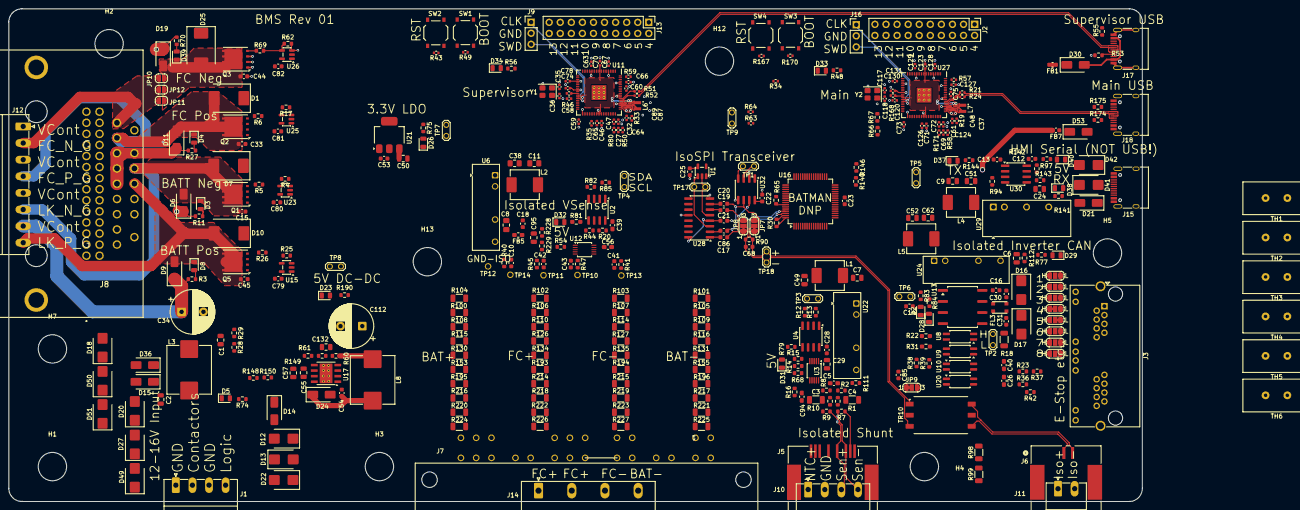
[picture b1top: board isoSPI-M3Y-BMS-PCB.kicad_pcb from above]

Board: 4 copper layers, 260.0 x 113.0 mm, 398 parts (0 on the bottom side), 267 nets.

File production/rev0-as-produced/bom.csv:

Designator,Footprint,Quantity,Value,LCSC Part #
"C1, C2, C24, C29, C55, C57, C6, C8, C96, C98, C99",0805,11,10uF,C440198
"C10, C12, C13, C14, C15, C16, C21, C22, C23, C25, C28, C33, C39, C41, C42, C43, C44, C45, C5, C54, C56, C76, C77, C79, C80, C83, C84, C85, C88, C93, C94, C97",0603,32,100nf,C14663
"C11, C132, C38, C49, C50, C51, C52, C62, C7, C9, C91, C92, C95",0805,13,22uF,C45783
"C112, C34, C69",CP_Radial_D10.0mm_P5.00mm,3,680uF,C46550429
"C117, C118, C35, C36",0402,4,15pF,C1548
"C120, C123, C124, C126, C127, C128, C129, C130, C131, C46, C58, C59, C60, C63, C64, C65, C66, C67, C70, C71, C73, C74, C75, C78",0402,24,100n,C1525
"C17, C18, C19, C20, C26, C27, C40, C86, C90",0603,9,1uF,C15849
"C3, C4",1206,2,4.7uF 50V,C29823
"C30, C31, C68",0603,3,100pF,C14858
"C32, C37, C47, C48, C61, C72, C87, C89",0402,8,4.7u,C23733
C53,0603,1,4.7uF,C19666
"C81, C82",1206,2,1nF,C9196
"D1, D10, D25, D7",D_SMC,4,SMCJ33CA,C224050
"D11, D14, D15, D21, D24, D30, D36, D39, D53, D6, D9",D_SMA,11,SS54,C22452
"D12, D13, D16, D17, D18, D20, D22, D27, D41, D42, D45, D46, D49, D50, D51",D_SMB,15,SMB6.8CA,C78395
"D19, D2, D3, D38, D4, D44, D8",0805,7,Green,C2297
"D23, D26, D29, D31, D32, D35, D40, D47, D5",0805,9,White,C34499
"D28, D33, D34, D37, D43",0805,5,Red,C84256
"FB1, FB7",0603,2,120Ω@100MHz,C14709
FB5,0603,1,600R@100MHz,C1002
FL3,FILTER-SMD_4P-L3.2-W2.5-BL,1,SDCW3225S-2-102TF,C192586
"GPIO44, GPIO45, GPIO46, GPIO47, TP10, TP11, TP12, TP13, TP14, TP22, TP23, TP24, TP25, TP26, TP27, TP28, TP29, TP30, TP31, TP32, TP33, TP34, TP35, TP36, TP37, TP38, TP41",TestPoint_THTPad_D1.5mm_Drill1.0mm,27,TP,
"J15, J17, J18",USB_C_Receptacle_HRO_TYPE-C-31-M-12,3,USB_C_Receptacle_USB2.0_16P,C2765186
J3,RJ45_Amphenol_RJHSE538X-02,1,8P8C_LED_Shielded_x2,C3010546
J6,CONN_SD-34912-001_02_MOL,1,OEM Connector,C587318
"JP10, JP11, JP12",SolderJumper-2_P1.3mm_Open_RoundedPad1.0x1.5mm,3,Jumper_2_Open,
"L1, L2, L4, L5, L9",L_Changjiang_FXL0630,5,6.8uh,C167221
"L3, L8",L_Changjiang_FXL1040,2,22uh 5.5A,C475917
"L6, L7",L_pol_2016,2,3.3uh,C42411119
"Q1, Q2, Q3, Q5",AO_DFN-8-1EP_5.55x5.2mm_P1.27mm_EP4.12x4.6mm,4,CRSM034N06L2,C467174
"R1, R10",0603,2,150r,C22808
"R100, R101, R102, R103, R104, R105, R106, R107, R108, R109, R110, R114, R115, R116, R126, R127, R130, R131, R134, R135, R153, R155, R193, R194, R195, R196, R214, R215, R216, R217, R218, R219, R220, R221, R222, R223, R224, R225, R226, R227, R98, R99",1206,42,1M,C17927
"R11, R146, R27, R3, R40, R41, R45, R47, R70, R74, R76",0603,11,24k,C23352
"R111, R112, R61, R7, R89, R9",0603,6,510r,C23193
"R113, R117, R12, R13, R14, R15, R174, R175, R20, R44, R53, R55, R82, R85, R93, R95, R96",0603,17,5.1k,C23186
"R118, R23, R36, R38, R42, R58, R71, R72, R78, R87, R92, R94, R97",0603,13,1k,C21190
"R140, R142, R143, R144, R148, R16, R190, R22, R29, R31, R48, R50, R54, R56, R66, R67, R68, R73, R75, R77, R79, R81, R83, R84, R86, R88, R91",0603,27,10k,C25804
"R149, R167, R168, R170, R34, R35, R43, R46, R49, R57, R59, R63, R64",0402,13,1k,C11702
"R150, R17, R25, R28, R4, R62",0603,6,100k,C25803
"R171, R19, R33, R80",0402,4,33r,C25105
R18,1206,1,120r,C17909
"R2, R37, R39, R8",0603,4,2.2k,C4190
"R21, R24, R51, R52",0402,4,22R,C25092
"R228, R229",0603,2,220r,C22962
"R26, R5, R6, R69",0603,4,33R,C23140
"R30, R90",0603,2,100r,C22775
R60,0402,1,3.3k,C25890
R65,0603,1,2.7k,C13167
"SW1, SW2, SW3, SW4",SW_Push_1P1T_XKB_TS-1187A,4,TS-1187A-B-A-B,C318884
"TH1, TH2, TH3, TH4, TH5, TH6",RV_Disc_D15.5mm_W7.5mm_P5.0mm,6,B59451C1130B070,C2762811
"TP1, TP15, TP16, TP17, TP18, TP19, TP2, TP20, TP21, TP3, TP39, TP4, TP40, TP42, TP5, TP6, TP7, TP8, TP9",TestPoint_2Pads_Pitch2.54mm_Pad1.5_Drill1.0mm,19,TestPoint_2Pole,
TR10,HM2113ZNLT,1,HM2113ZNLT,C5730533
U1,SOT-23-5,1,SN74LV1T08DBVR,C2682144
"U10, U20, U5, U7, U8, U9",SSOP-4_4.4x2.6mm_P1.27mm,6,LTV-217-B-G,C115450
"U11, U27",RP2350-QFN-80-1EP_10x10_P0.4mm_EP3.4x3.4mm_ThermalVias,2,RP2354B,C39843328
U12,TSSOP-10_3x3mm_P0.5mm,1,ADS1115,C37593
U13,SOP-8_6.62x9.15mm_P2.54mm,1,ISO1050DUB,C16428
"U14, U22, U24, U6",H0505S-1WR2,4,F0505S-1WR3,C7465182
"U15, U19",SOIC-8_3.9x4.9mm_P1.27mm,2,UCC27524DR,C465729
U17,TI_SO-PowerPAD-8_ThermalVias,1,TPS5430DDAR,C9864
"U18, U2, U30, U4",SOIC-8_3.9x4.9mm_P1.27mm,4,ISO1540,C179739
U21,SOT-223-3_TabPin2,1,AMS1117-3.3,C6186
U28,SOIC-16_3.9x9.9mm_P1.27mm,1,AM26LV32EIDR,C527448
U29,Converter_DCDC_TRACO_TRA3-xxxx_THT,1,B0505S-3WR2,C7500927
U3,VSSOP-10_3x3mm_P0.5mm,1,INA228,C5214669
U32,SOIC-8_3.9x4.9mm_P1.27mm,1,SP3485EN-L/TR,C8963
"Y1, Y2",Crystal_SMD_3225-4Pin_3.2x2.5mm,2,ABM8-272-T3,C20625731

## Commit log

2025-12-03 update gitignore
2025-12-03 update readme and add text to pcb
2025-12-03 connecting main mcu pins
2025-12-03 fix typo
2025-12-05 more
2025-12-05 routed dc-dc
2025-12-05 cleanup
2025-12-05 route ptc
2025-12-05 update hole size for PTC
2025-12-05 added more ground pins
2025-12-05 lots of updates
2025-12-07 more tweaks
2025-12-09 REV 0 Ordered!!!
2026-01-01 working on next revision now
2026-01-22 WIP - diverting after this to new mounting holes

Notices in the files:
README.md:
License: GPL v3
